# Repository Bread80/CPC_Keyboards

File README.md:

# Keyboards for Amstrad CPC Computers

This folder contains several designs for Amstrad computers, CPC464, CPC664 and CPC6128. Some can be fitted into the case of an existing machine, all can be used without a case as a replacement for, eg, a bare motherboard including recreations of original motherboards of replacement machines which use the same keyboard layout.

All of the above machines, CPC464, CPC664 and CPC6128, used an identical keyboard matrix although they had slight variations in connectors and pinouts. All of the boards here are suitable for using with any original motherboard. Most of the designs include jumpers or links which can be used to configure them to various mnotherboards. See the individual boards for more detail.

## Available Boards

### [Tactile Switch Keyboard](Tactile/README.md)

This was intended as a cheaper alternative to a full mechanical board. In practice the switches and keycaps used don't offer a huge saving in cost. However, the PCB is significantly smaller (and therefore cheaper), the design doesn't use diodes, and the keycaps can be home-printed and, therefore, modified to your preference.

This design is not (currently) fully documented.

[View...](Tactile/README.md)

### [CPC464 Mechanical with SMT Diodes](Keyswitch_CPC464_SMT/README.md)

As the heading suggests, this is a board using mechanical keyswitches, and which fits into an original CPC464 case (all variants, as far as we are aware). It includes connector pinouts for both styles of motherboard connector. Solder links allow for use with a CPC6128. See the schematics for how to wire to a CPC664.

The design uses SMT diodes which may present a soldering challenge to some, but the diodes and footprints have been chosen to make soldering as easy as possible.

[View...](Keyswitch_CPC464_SMT/README.md)

### [CPC6128 Mechanical with SMT Diodes](Keyswitch_CPC6128_SMT/README.md)

This board is still at the design stage and NOT suitable for production.

[View...](Keyswitch_CPC6128_SMT/README.md)

## Licence

All designs are licenced under CERN-OHL-P.

You are welcome you sell items for cost plus reasonable postage fees. This allows you to pass on any overages from your PCB fab's minumum order levels. If you want to sell items for profit please talk to us first.

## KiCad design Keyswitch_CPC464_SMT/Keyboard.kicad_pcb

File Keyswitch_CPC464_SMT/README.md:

# CPC464 Mechanical Keyboard (with SMT Diodes)

This project is for an replacement keyboard for an Amstrad CPC464 using Cherry MX compatible keyswitches.

The board is suitable for mounting within an existing CPC464 case and includes connections suitable for both the single row 19/20-pin inline PCB type keyboard and the dual 10-pin connectors used by later membrane keyboards. It can also be used free standing, either with a CPC464 or CPC6128 - jumpers footprints are included to allow remapping of the dual 10-pin connectors. (The keyboard could also be used with a CPC664 but the lines will need remapping between the keyboard and motherboard. The schematic includes details). A third connector footprint is provided at the rear of the board with identical pinout to the 2x10-pin connector (and remapped via the same jumpers). This connector is intended to make the PCB easier to use as a free-standing board when, for example, using with a bare motherboard outside of a case.

Footprints allow either direct soldering of the keyswitches to the board, or the use of MX hotswap sockets. Hotswap sockets allow keyswitches to be more easily swapped for different types or between boards. The board accepts either 3-pin or 5-pin keyswitches but NOTE: There is currently no mounting plate available. We therefore recommend only using 5-pin keyswitches, and NOT 3-pin ones (5-pin switches have two extra mounting lugs on the rear).

The space bar has been reduced in width from the original 9u to a modern standard 7u. The space freed by this has allowed the addition of two 'bonus' keys. These can be mapped, via jumpers, to the main connectors for reading by the host computer, or can be connected to external hardware via the same jumpers.

When fitted into an Amstrad CPC464 case there is a slight gap (0.5u wide, where 1u is one standard key width) to the right of the Enter key. This is, sadly, unavoidable due to available keycap sizes.

## Purchase PCBs

You can download the gerbers from within the repository or purchase PCBs via PCBWay Shared Projects at https://www.pcbway.com/project/shareproject/Mechanical_Keyboard_for_Amstrad_CPC464_e66db4b2.html Disclaimer: we get a small commission if you purchase from PCBWay Shared Projects. This commission helps to fund our other open source projects.

## Bill or Materials (BoM)

(This list does not include connectors. See the section below for some connection options).

|Reference|Value|Package|Qty|Notes|
|---------|-----|-------|---|-----|
|D0-D71,D79,D901,D902|1N4148W|SOD-123|75|If buying from a specialist mechanical keyboard retailer these will be the only surface mount diodes available. We recommend buying a few spares as these are very small and easy to lose.|
|SW0-SW71,SW79,SW901,SW902|MX Hotswap Sockets||75|Optional. Make sure you get the MX type.|
|SW0-SW71,SW79,SW901,SW902|MX Compatible keyswitches||75|Lots of options available. As noted above these should be 5-pin switches.|
|SW0-SW71,SW79,SW901,SW902|MX Compatible keycaps||75|Again of options available. See below for some advice.|
|ST1,ST2|Stabiliser 2u|PCB Mount|2|Use 'PCB Mount'/'screw in' type (NOT plate mount)	Stabilisers are usually supplied in sets which include all necessary parts including mounting screws. Each set will contain more than you need to this project, but make sure you get a set which includes a 7u wire for the space bar.|
|ST3|Stabiliser 7u|PCB Mount|1|(See notes for 2u stabilisers above).|

### Feet

If the board is used free-standing you will probably want to add some feet. The board includes 6(No) M3 mounting holes suitable for this. We would suggest rubber feet at the front and stand-offs at the rear (possibly with rubber feet on the end) to provide some 'raking' to the board.

## Assembly

Begin by orienting yourself to the board and, in particular, which side is the top and which the bottom. The top of the board boards the square outlines of the keyswitches, the bottom has the footprints for the hotswap sockets and diodes. Diodes, hotswap sockets (if used) and keyswitches (if not using sockets) are all soldered to the bottom of the board.

We suggest the following assembly sequence.

1. Diodes

Diodes must be installed in the correct orientation. If examined closely you will notice a white line across one end of the diode. On the PCB this end all the diodes must point towards the front (space bar end) of the board. It might be wise to test a few with a multimeter to verify you are have this correct.

2. Hotswap sockets (if using them)

Orient each socket to match the silkscreen and so that the two lugs occupy the holes, then solder each pin.

It's worthwhile checking each socket is fully seated into the board by reheating each pin which pushing the socket with a finger - but take care not to burn your finger! We like to solder all the sockets, then go over one end of every socket. Then, once they have cooled, do the same for the other end of every socket.

3. Connectors and Jumpers (depending on your chosen options - see below)

For jumpers use some wire offcuts - perhaps resistor leads from a previous project?

4. Stabilisers

Check the manufacturers instructions. Pre-assembled ones are fairly straightforward, others are an IQ test which we often fail at on the first go. If the key doesn't press down properly you failed too.

5. Keyswitches (if not using sockets)

These are pretty straightforward. Insert each so that the pins are located in the plated (metalised) holes and fully pushed 'home'. Solder both pins. Double check they are fully seated and, if necessary, reheat while pushing down on the switch.

6. Keyswitches (if using sockets)

This one is easy! Insert the keyswitches, but make sure the pins are mounted into the sockets (this may sound dumb, but they are easily bent).

## Jumper Settings

'Bridging' a solder link entails soldering some bare wire between two pins on the link.

If connecting to a '464 bridge LK2 and the two pins at the '464' end of LK1 (as shown in the photo).

If connecting to a '6128 bridge LK3 and the two pins at the '6128' end of LK3.

(If using the board freestanding and want the flexibility to move it between computers you could also use pin-header with 'shunts' to bridge them. If so you may want to locate them on the top-side of the board).

## Bonus Switches

To map the bonus switches to joystick 1 fire buttons, short the connectors as shown in the photo.

To use as separate switches make connections to three holes indicated by the arrows.

## Installation

The keyboard is attached to the case with five or six screws (depending on the case revision) and replacement is straightforward. Take care not to overtighten the screws as the threads in the plastic case are easy to strip.

The spade terminal ground connection cannot be connected to the new PCB and will need to be covered with electrical insulation tape or similar to prevent it shorting anything.

## Connecting to the motherboard

Connection options depend on your motherboard revision. We are open to feedback and suggestions for better options.

### Single Row Motherboards (PCB style keyboards)

Amstrad appear to have used two different connector styles over the life of the machine. Sadly neither of these seem to be still available. The best option is probably replacing the motherboard header with something which is available, and directly soldering wires to the keyboard PCB (as per original Amstrad keyboards).

### Double Row Motherboards (membrane style keyboards)

PCBs are available which can slot into the motherboard connectors. We have our own available at https://github.com/Bread80/Keyboard-FPC10  The motherboard connectors are single sided and the PCBs will need to be assembled to match. Note that these PCBs must be manufactured to a suitable thickness for inserting into the sockets.

Our preference is to use FFC/FPC cables (with 2.54mm pin pitch) to connect these to the keyboard, the other end being direct soldered to the board.

## Keycaps

There is, obviously, a wide selection of keycaps available. In the board shown in the photos we've used the lovely Amstrad inspired set available at https://finalkeystudio.com/products/amstrad-cpc-464-keycaps-set which has both '464 and '6128 inspired options. Sadly the set  doesn't cover ever key you'll need (note the CLR and DEL keys in the photos) but there are plenty of other keys which can be used to substitute. The set also uses 'standard' layout for (eg) symbols rather than (any of) the Amstrad layout(s). (We have no connection to the designer or seller, and can't offer buying advice, but we do love the keycaps).

When selecting a set you'll need one which includes the following key widths:
|Key|Width|
|---|-----|
|Tab|1.5u|
|Caps|1.75u|
|Left Shift|2.25u|
|Backspace|1u|
|Enter|ISO standard|
|Right Shift|1.75u|
|Space bar|7u|

It's also worth noting that you're unlikely to find a set which matches the Amstrad symbol layout. If rearranging keys note that keycap profiles are different for every row and swapping keys between rows may not be ideal.

Rather than re-arranging the keys the Amstrad firmware has support for remapping the layout in software. This is (currently) left as an exercise for the reader.

## Schematic

## Licence

CERN-OHL-P

You are welcome you sell items for cost plus reasonable postage fees. This allows you to pass on any overages from your PCB fab's minimum order levels. If you want to sell items for profit please talk to us first.

## More Images

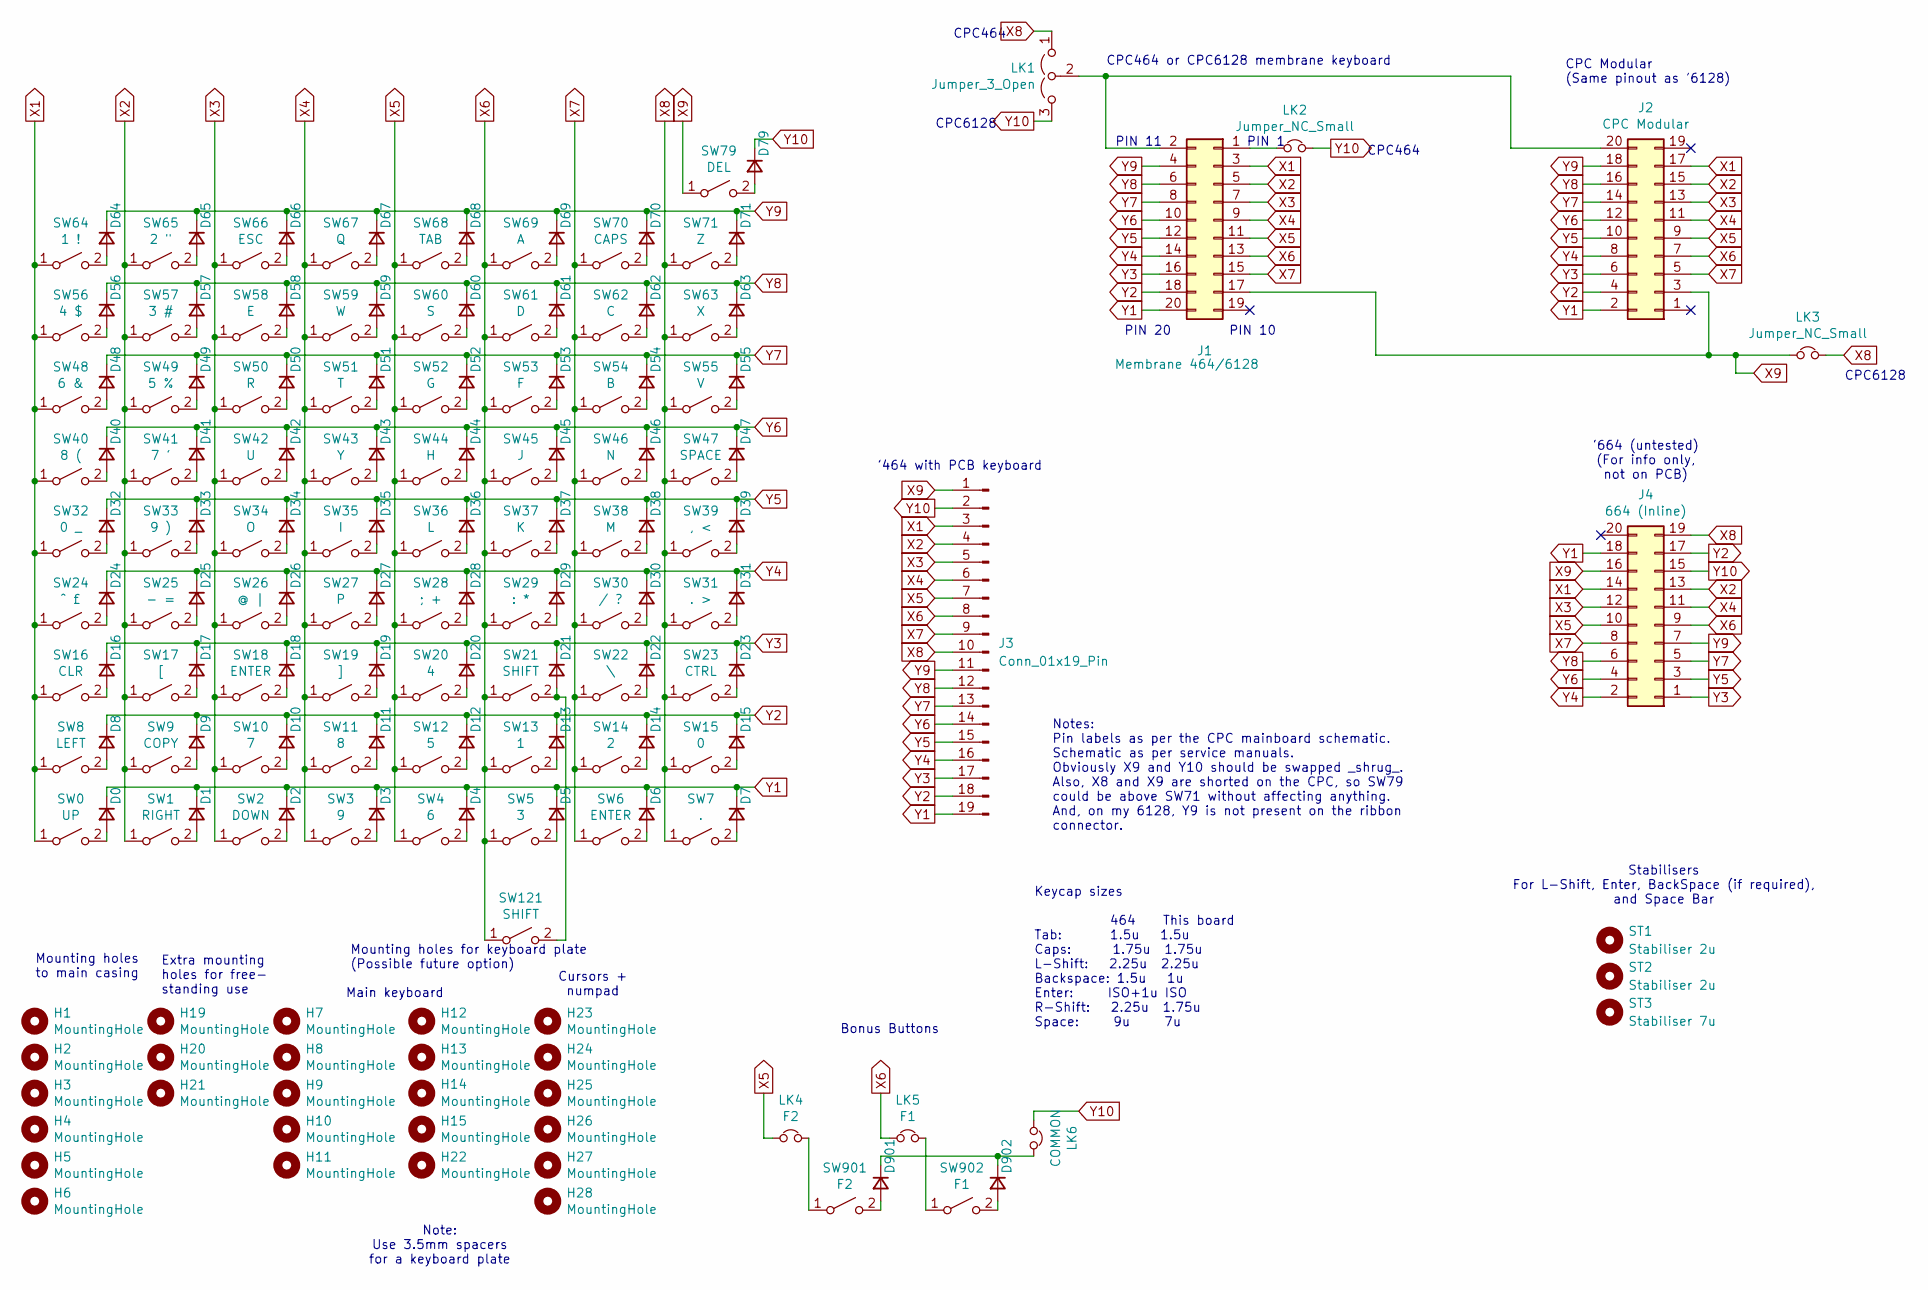
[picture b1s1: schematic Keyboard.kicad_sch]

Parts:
D0, D1, D2, D3, D4, D5, D6, D7, D8, D9, D10, D11, D12, D13, D14, D15, D16, D17, D18, D19, D20, D21, D22, D23, D24, D25, D26, D27, D28, D29, D30, D31, D32, D33, D34, D35, D36, D37, D38, D39, D40, D41, D42, D43, D44, D45, D46, D47, D48, D49, D50, D51, D52, D53, D54, D55, D56, D57, D58, D59, D60, D61, D62, D63, D64, D65, D66, D67, D68, D69, D70, D71, D79, D901, D902: 1N4148; D_SOD-123-Handsolder
H1, H3, H4, H6: MountingHole; MountingHole4.3mmx5.3mmNPTH
H2, H19, H20, H21: MountingHole; MountingHole_4.3mm_M4_DIN965
H5: MountingHole; MountingHole_3.2mm_M3_DIN965
H7, H8, H9, H10, H11, H12, H13, H14, H15, H22, H23, H24, H25, H26, H27, H28: MountingHole; MountingHole_2.2mm_M2_DIN965
J1: Membrane 464/6128; PinHeader_2x10_P2.54mm_Vertical
J2: CPC Modular; IDC-Header_2x10_P2.54mm_Vertical
J3: Conn_01x19_Pin; PinHeader_1x19_P2.54mm_Vertical
J4: 664 (Inline); IDC-Header_2x10_P2.54mm_Vertical
LK1: Jumper_3_Open; PinHeader_1x03_P2.54mm_Vertical
LK2, LK3: Jumper_NC_Small; PinHeader_1x02_P2.54mm_Vertical
LK4: F2; PinHeader_1x02_P2.54mm_Vertical
LK5: F1; PinHeader_1x02_P2.54mm_Vertical
LK6: COMMON; PinHeader_1x02_P2.54mm_Vertical
ST1, ST2: Stabiliser 2u; Stabilizer_MX_2u
ST3: Stabiliser 7u; Stabilizer_MX_7u
SW0: UP; Kailh_socket_MX_optional
SW1: RIGHT; Kailh_socket_MX_optional
SW2: DOWN; Kailh_socket_MX_optional
SW3: 9; Kailh_socket_MX_optional
SW4: 6; Kailh_socket_MX_optional
SW5: 3; Kailh_socket_MX_optional
SW6, SW18: ENTER; Kailh_socket_MX_optional
SW7: .; Kailh_socket_MX_optional
SW8: LEFT; Kailh_socket_MX_optional
SW9: COPY; Kailh_socket_MX_optional
SW10: 7; Kailh_socket_MX_optional
SW11: 8; Kailh_socket_MX_optional
SW12: 5; Kailh_socket_MX_optional
SW13: 1; Kailh_socket_MX_optional
SW14: 2; Kailh_socket_MX_optional
SW15: 0; Kailh_socket_MX_optional
SW16: CLR; Kailh_socket_MX_optional
SW17: [; Kailh_socket_MX_optional
SW19: ]; Kailh_socket_MX_optional
SW20: 4; Kailh_socket_MX_optional
SW21, SW121: SHIFT; Kailh_socket_MX_optional
SW22: \; Kailh_socket_MX_optional
SW23: CTRL; Kailh_socket_MX_optional
SW24: ^ £; Kailh_socket_MX_optional
SW25: - =; Kailh_socket_MX_optional
SW26: @ |; Kailh_socket_MX_optional
SW27: P; Kailh_socket_MX_optional
SW28: ; +; Kailh_socket_MX_optional
SW29: : *; Kailh_socket_MX_optional
SW30: / ?; Kailh_socket_MX_optional
SW31: . >; Kailh_socket_MX_optional
SW32: 0 _; Kailh_socket_MX_optional
SW33: 9 ); Kailh_socket_MX_optional
SW34: O; Kailh_socket_MX_optional
SW35: I; Kailh_socket_MX_optional
SW36: L; Kailh_socket_MX_optional
SW37: K; Kailh_socket_MX_optional
SW38: M; Kailh_socket_MX_optional
SW39: , <; Kailh_socket_MX_optional
SW40: 8 (; Kailh_socket_MX_optional
SW41: 7 '; Kailh_socket_MX_optional
SW42: U; Kailh_socket_MX_optional
SW43: Y; Kailh_socket_MX_optional
SW44: H; Kailh_socket_MX_optional
SW45: J; Kailh_socket_MX_optional
SW46: N; Kailh_socket_MX_optional
SW47: SPACE; Kailh_socket_MX_optional
SW48: 6 &; Kailh_socket_MX_optional
SW49: 5 %; Kailh_socket_MX_optional
SW50: R; Kailh_socket_MX_optional
SW51: T; Kailh_socket_MX_optional
SW52: G; Kailh_socket_MX_optional
SW53: F; Kailh_socket_MX_optional
SW54: B; Kailh_socket_MX_optional
SW55: V; Kailh_socket_MX_optional
SW56: 4 $; Kailh_socket_MX_optional
SW57: 3 #; Kailh_socket_MX_optional
SW58: E; Kailh_socket_MX_optional
SW59: W; Kailh_socket_MX_optional
SW60: S; Kailh_socket_MX_optional
SW61: D; Kailh_socket_MX_optional
SW62: C; Kailh_socket_MX_optional
SW63: X; Kailh_socket_MX_optional
SW64: 1 !; Kailh_socket_MX_optional
SW65: 2 "; Kailh_socket_MX_optional
SW66: ESC; Kailh_socket_MX_optional
SW67: Q; Kailh_socket_MX_optional
SW68: TAB; Kailh_socket_MX_optional
SW69: A; Kailh_socket_MX_optional
SW70: CAPS; Kailh_socket_MX_optional
SW71: Z; Kailh_socket_MX_optional
SW79: DEL; Kailh_socket_MX_optional
SW901: F2; Kailh_socket_MX_optional
SW902: F1; Kailh_socket_MX_optional

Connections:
unnamed: D0.2 (A), SW0.2 (B)
unnamed: D1.2 (A), SW1.2 (B)
unnamed: D2.2 (A), SW2.2 (B)
unnamed: D3.2 (A), SW3.2 (B)
unnamed: D4.2 (A), SW4.2 (B)
unnamed: D5.2 (A), SW5.2 (B)
unnamed: D6.2 (A), SW6.2 (B)
unnamed: D7.2 (A), SW7.2 (B)
unnamed: D8.2 (A), SW8.2 (B)
unnamed: D9.2 (A), SW9.2 (B)
unnamed: D10.2 (A), SW10.2 (B)
unnamed: D11.2 (A), SW11.2 (B)
unnamed: D12.2 (A), SW12.2 (B)
unnamed: D13.2 (A), SW13.2 (B)
unnamed: D14.2 (A), SW14.2 (B)
unnamed: D15.2 (A), SW15.2 (B)
unnamed: D16.2 (A), SW16.2 (B)
unnamed: D17.2 (A), SW17.2 (B)
unnamed: D18.2 (A), SW18.2 (B)
unnamed: D19.2 (A), SW19.2 (B)
unnamed: D20.2 (A), SW20.2 (B)
unnamed: D21.2 (A), SW21.2 (B), SW121.2 (B)
unnamed: D22.2 (A), SW22.2 (B)
unnamed: D23.2 (A), SW23.2 (B)
unnamed: D24.2 (A), SW24.2 (B)
unnamed: D25.2 (A), SW25.2 (B)
unnamed: D26.2 (A), SW26.2 (B)
unnamed: D27.2 (A), SW27.2 (B)
unnamed: D28.2 (A), SW28.2 (B)
unnamed: D29.2 (A), SW29.2 (B)
unnamed: D30.2 (A), SW30.2 (B)
unnamed: D31.2 (A), SW31.2 (B)
unnamed: D32.2 (A), SW32.2 (B)
unnamed: D33.2 (A), SW33.2 (B)
unnamed: D34.2 (A), SW34.2 (B)
unnamed: D35.2 (A), SW35.2 (B)
unnamed: D36.2 (A), SW36.2 (B)
unnamed: D37.2 (A), SW37.2 (B)
unnamed: D38.2 (A), SW38.2 (B)
unnamed: D39.2 (A), SW39.2 (B)
unnamed: D40.2 (A), SW40.2 (B)
unnamed: D41.2 (A), SW41.2 (B)
unnamed: D42.2 (A), SW42.2 (B)
unnamed: D43.2 (A), SW43.2 (B)
unnamed: D44.2 (A), SW44.2 (B)
unnamed: D45.2 (A), SW45.2 (B)
unnamed: D46.2 (A), SW46.2 (B)
unnamed: D47.2 (A), SW47.2 (B)
unnamed: D48.2 (A), SW48.2 (B)
unnamed: D49.2 (A), SW49.2 (B)
unnamed: D50.2 (A), SW50.2 (B)
unnamed: D51.2 (A), SW51.2 (B)
unnamed: D52.2 (A), SW52.2 (B)
unnamed: D53.2 (A), SW53.2 (B)
unnamed: D54.2 (A), SW54.2 (B)
unnamed: D55.2 (A), SW55.2 (B)
unnamed: D56.2 (A), SW56.2 (B)
unnamed: D57.2 (A), SW57.2 (B)
unnamed: D58.2 (A), SW58.2 (B)
unnamed: D59.2 (A), SW59.2 (B)
unnamed: D60.2 (A), SW60.2 (B)
unnamed: D61.2 (A), SW61.2 (B)
unnamed: D62.2 (A), SW62.2 (B)
unnamed: D63.2 (A), SW63.2 (B)
unnamed: D64.2 (A), SW64.2 (B)
unnamed: D65.2 (A), SW65.2 (B)
unnamed: D66.2 (A), SW66.2 (B)
unnamed: D67.2 (A), SW67.2 (B)
unnamed: D68.2 (A), SW68.2 (B)
unnamed: D69.2 (A), SW69.2 (B)
unnamed: D70.2 (A), SW70.2 (B)
unnamed: D71.2 (A), SW71.2 (B)
unnamed: D79.2 (A), SW79.2 (B)
unnamed: D901.2 (A), SW901.2 (B)
unnamed: D901.1 (K), D902.1 (K), LK6.1
unnamed: D902.2 (A), SW902.2 (B)
unnamed: J1.1, LK2.2
unnamed: J1.2, J2.20, LK1.2 (C)
unnamed: LK4.1, SW901.1 (A)
unnamed: LK5.1, SW902.1 (A)
X1: J1.3, J2.17, J3.3, J4.14, SW0.1 (A), SW8.1 (A), SW16.1 (A), SW24.1 (A), SW32.1 (A), SW40.1 (A), SW48.1 (A), SW56.1 (A), SW64.1 (A)
X2: J1.5, J2.15, J3.4, J4.13, SW1.1 (A), SW9.1 (A), SW17.1 (A), SW25.1 (A), SW33.1 (A), SW41.1 (A), SW49.1 (A), SW57.1 (A), SW65.1 (A)
X3: J1.7, J2.13, J3.5, J4.12, SW2.1 (A), SW10.1 (A), SW18.1 (A), SW26.1 (A), SW34.1 (A), SW42.1 (A), SW50.1 (A), SW58.1 (A), SW66.1 (A)
X4: J1.9, J2.11, J3.6, J4.11, SW3.1 (A), SW11.1 (A), SW19.1 (A), SW27.1 (A), SW35.1 (A), SW43.1 (A), SW51.1 (A), SW59.1 (A), SW67.1 (A)
X5: J1.11, J2.9, J3.7, J4.10, LK4.2, SW4.1 (A), SW12.1 (A), SW20.1 (A), SW28.1 (A), SW36.1 (A), SW44.1 (A), SW52.1 (A), SW60.1 (A), SW68.1 (A)
X6: J1.13, J2.7, J3.8, J4.9, LK5.2, SW5.1 (A), SW13.1 (A), SW21.1 (A), SW29.1 (A), SW37.1 (A), SW45.1 (A), SW53.1 (A), SW61.1 (A), SW69.1 (A), SW121.1 (A)
X7: J1.15, J2.5, J3.9, J4.8, SW6.1 (A), SW14.1 (A), SW22.1 (A), SW30.1 (A), SW38.1 (A), SW46.1 (A), SW54.1 (A), SW62.1 (A), SW70.1 (A)
X8: J3.10, J4.19, LK1.1 (A), LK3.1, SW7.1 (A), SW15.1 (A), SW23.1 (A), SW31.1 (A), SW39.1 (A), SW47.1 (A), SW55.1 (A), SW63.1 (A), SW71.1 (A)
X9: J1.17, J2.3, J3.1, J4.16, LK3.2, SW79.1 (A)
Y1: D0.1 (K), D1.1 (K), D2.1 (K), D3.1 (K), D4.1 (K), D5.1 (K), D6.1 (K), D7.1 (K), J1.20, J2.2, J3.19, J4.18
Y2: D8.1 (K), D9.1 (K), D10.1 (K), D11.1 (K), D12.1 (K), D13.1 (K), D14.1 (K), D15.1 (K), J1.18, J2.4, J3.18, J4.17
Y3: D16.1 (K), D17.1 (K), D18.1 (K), D19.1 (K), D20.1 (K), D21.1 (K), D22.1 (K), D23.1 (K), J1.16, J2.6, J3.17, J4.1
Y4: D24.1 (K), D25.1 (K), D26.1 (K), D27.1 (K), D28.1 (K), D29.1 (K), D30.1 (K), D31.1 (K), J1.14, J2.8, J3.16, J4.2
Y5: D32.1 (K), D33.1 (K), D34.1 (K), D35.1 (K), D36.1 (K), D37.1 (K), D38.1 (K), D39.1 (K), J1.12, J2.10, J3.15, J4.3
Y6: D40.1 (K), D41.1 (K), D42.1 (K), D43.1 (K), D44.1 (K), D45.1 (K), D46.1 (K), D47.1 (K), J1.10, J2.12, J3.14, J4.4
Y7: D48.1 (K), D49.1 (K), D50.1 (K), D51.1 (K), D52.1 (K), D53.1 (K), D54.1 (K), D55.1 (K), J1.8, J2.14, J3.13, J4.5
Y8: D56.1 (K), D57.1 (K), D58.1 (K), D59.1 (K), D60.1 (K), D61.1 (K), D62.1 (K), D63.1 (K), J1.6, J2.16, J3.12, J4.6
Y9: D64.1 (K), D65.1 (K), D66.1 (K), D67.1 (K), D68.1 (K), D69.1 (K), D70.1 (K), D71.1 (K), J1.4, J2.18, J3.11, J4.7
Y10: D79.1 (K), J3.2, J4.15, LK1.3 (B), LK2.1, LK6.2

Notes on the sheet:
Cursors + numpad
CPC464
PIN 11
Mounting holes to main casing
PIN 10
PIN 1
Extra mounting holes for free- standing use
Keycap sizes 464 This board Tab: 1.5u 1.5u Caps: 1.75u 1.75u L-Shift: 2.25u 2.25u Backspace: 1.5u 1u Enter: ISO+1u ISO R-Shift: 2.25u 1.75u Space: 9u 7u
CPC6128
Stabilisers For L-Shift, Enter, BackSpace (if required), and Space Bar
Note: Use 3.5mm spacers for a keyboard plate
'464 with PCB keyboard
Notes: Pin labels as per the CPC mainboard schematic. Schematic as per service manuals. Obviously X9 and Y10 should be swapped _shrug_. Also, X8 and X9 are shorted on the CPC, so SW79 could be above SW71 without affecting anything. And, on my 6128, Y9 is not present on the ribbon connector.
'664 (untested) (For info only, not on PCB)
Bonus Buttons
CPC464 or CPC6128 membrane keyboard
Main keyboard
CPC Modular (Same pinout as '6128)
PIN 20
Mounting holes for keyboard plate (Possible future option)

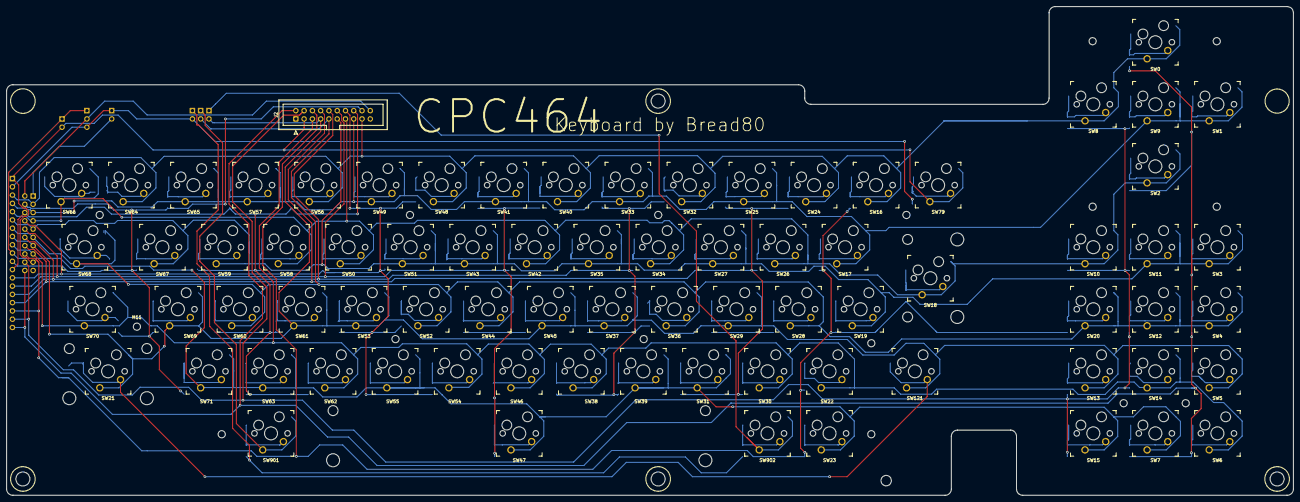
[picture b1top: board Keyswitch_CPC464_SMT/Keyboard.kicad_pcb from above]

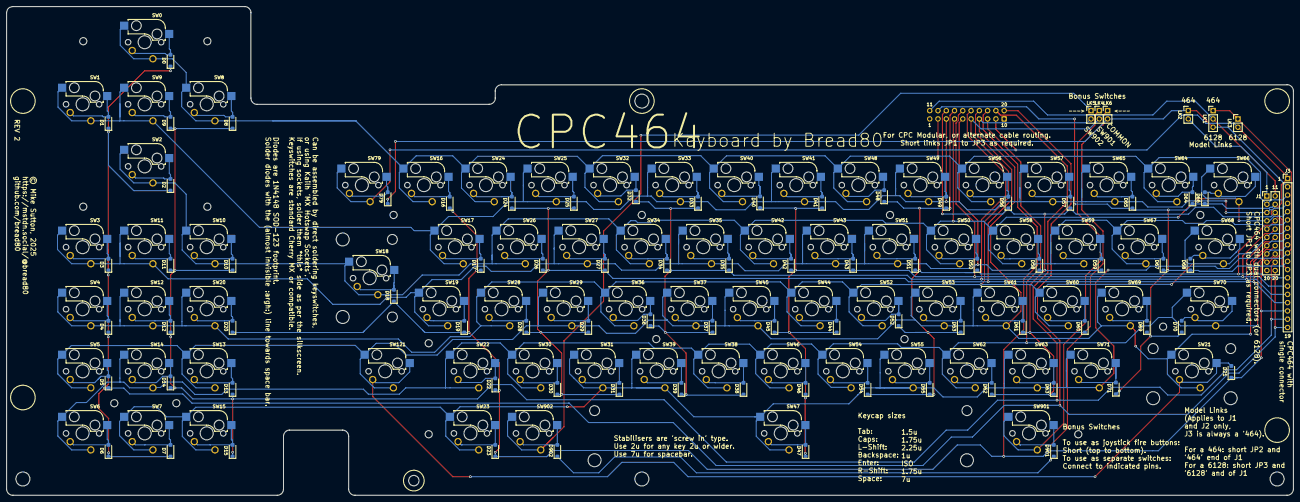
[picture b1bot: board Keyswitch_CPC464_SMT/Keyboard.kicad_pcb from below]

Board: 2 copper layers, 395.0 x 150.0 mm, 188 parts (83 on the bottom side), 99 nets.

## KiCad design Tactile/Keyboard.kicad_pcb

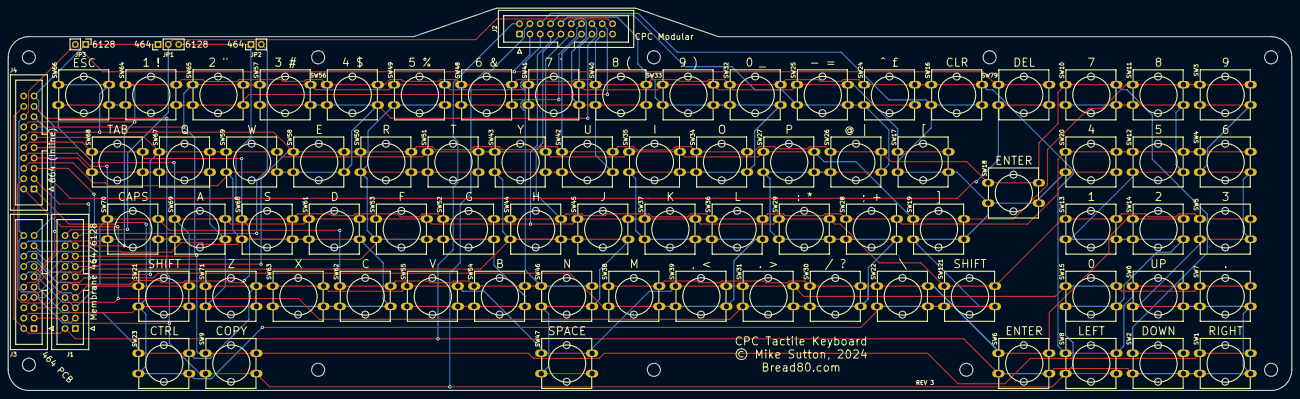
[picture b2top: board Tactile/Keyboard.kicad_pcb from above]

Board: 2 copper layers, 315.6 x 94.0 mm, 91 parts (0 on the bottom side), 21 nets.

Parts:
H1, H2, H3, H4, H5, H11, H12, H13, H14, H15: MountingHole; MountingHole_3.2mm_M3_DIN965
J1: Membrane 464/6128; IDC-Header_2x10_P2.54mm_Vertical
J2: CPC Modular; IDC-Header_2x10_P2.54mm_Vertical
J3: 464 PCB (Inline); IDC-Header_2x10_P2.54mm_Vertical
J4: 664 (Inline); IDC-Header_2x10_P2.54mm_Vertical
JP1: Jumper_3_Open; PinHeader_1x03_P2.54mm_Vertical
JP2, JP3: Jumper_NC_Small; PinHeader_1x02_P2.54mm_Vertical
SW0: UP; SKHCBEA010
SW1: RIGHT; SKHCBEA010
SW2: DOWN; SKHCBEA010
SW3: 9; SKHCBEA010
SW4: 6; SKHCBEA010
SW5: 3; SKHCBEA010
SW6, SW18: ENTER; SKHCBEA010
SW7: .; SKHCBEA010
SW8: LEFT; SKHCBEA010
SW9: COPY; SKHCBEA010
SW10: 7; SKHCBEA010
SW11: 8; SKHCBEA010
SW12: 5; SKHCBEA010
SW13: 1; SKHCBEA010
SW14: 2; SKHCBEA010
SW15: 0; SKHCBEA010
SW16: CLR; SKHCBEA010
SW17: [; SKHCBEA010
SW19: ]; SKHCBEA010
SW20: 4; SKHCBEA010
SW21, SW121: SHIFT; SKHCBEA010
SW22: \; SKHCBEA010
SW23: CTRL; SKHCBEA010
SW24: ^ £; SKHCBEA010
SW25: - =; SKHCBEA010
SW26: @ |; SKHCBEA010
SW27: P; SKHCBEA010
SW28: ; +; SKHCBEA010
SW29: : *; SKHCBEA010
SW30: / ?; SKHCBEA010
SW31: . >; SKHCBEA010
SW32: 0 _; SKHCBEA010
SW33: 9 ); SKHCBEA010
SW34: O; SKHCBEA010
SW35: I; SKHCBEA010
SW36: L; SKHCBEA010
SW37: K; SKHCBEA010
SW38: M; SKHCBEA010
SW39: , <; SKHCBEA010
SW40: 8 (; SKHCBEA010
SW41: 7 '; SKHCBEA010
SW42: U; SKHCBEA010
SW43: Y; SKHCBEA010
SW44: H; SKHCBEA010
SW45: J; SKHCBEA010
SW46: N; SKHCBEA010
SW47: SPACE; SKHCBEA010
SW48: 6 &; SKHCBEA010
SW49: 5 %; SKHCBEA010
SW50: R; SKHCBEA010
SW51: T; SKHCBEA010
SW52: G; SKHCBEA010
SW53: F; SKHCBEA010
SW54: B; SKHCBEA010
SW55: V; SKHCBEA010
SW56: 4 $; SKHCBEA010
SW57: 3 #; SKHCBEA010
SW58: E; SKHCBEA010
SW59: W; SKHCBEA010
SW60: S; SKHCBEA010
SW61: D; SKHCBEA010
SW62: C; SKHCBEA010
SW63: X; SKHCBEA010
SW64: 1 !; SKHCBEA010
SW65: 2 "; SKHCBEA010
SW66: ESC; SKHCBEA010
SW67: Q; SKHCBEA010
SW68: TAB; SKHCBEA010
SW69: A; SKHCBEA010
SW70: CAPS; SKHCBEA010
SW71: Z; SKHCBEA010
SW79: DEL; SKHCBEA010

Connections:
unnamed: J1.19, JP2.2
unnamed: J1.20, J2.20, JP1.2
X1: J1.17, J2.17, J3.18, J4.14, SW0.1, SW8.1, SW16.1, SW24.1, SW32.1, SW40.1, SW48.1, SW56.1, SW64.1
X2: J1.15, J2.15, J3.17, J4.13, SW1.1, SW9.1, SW17.1, SW25.1, SW33.1, SW41.1, SW49.1, SW57.1, SW65.1
X3: J1.13, J2.13, J3.16, J4.12, SW2.1, SW10.1, SW18.1, SW26.1, SW34.1, SW42.1, SW50.1, SW58.1, SW66.1
X4: J1.11, J2.11, J3.15, J4.11, SW3.1, SW11.1, SW19.1, SW27.1, SW35.1, SW43.1, SW51.1, SW59.1, SW67.1
X5: J1.9, J2.9, J3.14, J4.10, SW4.1, SW12.1, SW20.1, SW28.1, SW36.1, SW44.1, SW52.1, SW60.1, SW68.1
X6: J1.7, J2.7, J3.13, J4.9, SW5.1, SW13.1, SW21.1, SW29.1, SW37.1, SW45.1, SW53.1, SW61.1, SW69.1, SW121.1
X7: J1.5, J2.5, J3.12, J4.8, SW6.1, SW14.1, SW22.1, SW30.1, SW38.1, SW46.1, SW54.1, SW62.1, SW70.1
X8: J3.11, J4.19, JP1.1, JP3.1, SW7.1, SW15.1, SW23.1, SW31.1, SW39.1, SW47.1, SW55.1, SW63.1, SW71.1
X9: J1.3, J2.3, J3.20, J4.16, JP3.2, SW79.1
Y1: J1.2, J2.2, J3.2, J4.18, SW0.2, SW1.2, SW2.2, SW3.2, SW4.2, SW5.2, SW6.2, SW7.2
Y2: J1.4, J2.4, J3.3, J4.17, SW8.2, SW9.2, SW10.2, SW11.2, SW12.2, SW13.2, SW14.2, SW15.2
Y3: J1.6, J2.6, J3.4, J4.1, SW16.2, SW17.2, SW18.2, SW19.2, SW20.2, SW21.2, SW22.2, SW23.2, SW121.2
Y4: J1.8, J2.8, J3.5, J4.2, SW24.2, SW25.2, SW26.2, SW27.2, SW28.2, SW29.2, SW30.2, SW31.2
Y5: J1.10, J2.10, J3.6, J4.3, SW32.2, SW33.2, SW34.2, SW35.2, SW36.2, SW37.2, SW38.2, SW39.2
Y6: J1.12, J2.12, J3.7, J4.4, SW40.2, SW41.2, SW42.2, SW43.2, SW44.2, SW45.2, SW46.2, SW47.2
Y7: J1.14, J2.14, J3.8, J4.5, SW48.2, SW49.2, SW50.2, SW51.2, SW52.2, SW53.2, SW54.2, SW55.2
Y8: J1.16, J2.16, J3.9, J4.6, SW56.2, SW57.2, SW58.2, SW59.2, SW60.2, SW61.2, SW62.2, SW63.2
Y9: J1.18, J2.18, J3.10, J4.7, SW64.2, SW65.2, SW66.2, SW67.2, SW68.2, SW69.2, SW70.2, SW71.2
Y10: J3.19, J4.15, JP1.3, JP2.1, SW79.2

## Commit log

2025-09-02 Tweaking images
2025-09-02 More image tweaks
2025-09-02 More image tests
2025-09-05 Add link to PCBWay Shared Projects

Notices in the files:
Keyswitch_CPC464_SMT/Keyboard.kicad_pcb:
© Mike Sutton, 2025
Tactile/Keyboard.kicad_pcb:
© Mike Sutton, 2024
